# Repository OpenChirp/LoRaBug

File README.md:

# Specs
* TI CC2650 MCU with BLE and 802.15.4 support
* SX1276 LoRa radio
* Provide 500mA 3.3V (3.3-3.4V) from USB.

# Board Details
* Pin mappings are detailed in the spreadsheet found [here](https://docs.google.com/spreadsheets/d/1lk55i37ZrpTx_7zy1oA4uAmHo3XsjOCir2L95xEN9fU/edit?usp=sharing).
* Board physical dimensions and header placement can be found [here](https://docs.google.com/drawings/d/1snO6Dwncqp3OL73APsFgQn0SESudZwlPjw8W5KeOZVo/edit?usp=sharing).
* You can find other information, such as the schematic and board renderings, in the [Info](Info/) directory.

# Firmware Notes
* You can detect the presence of a USB by checking if the FTDI TX and RX
  pins are high. When the FTDI chip is activated, it pulls the TX and RX
  lines high.
  Additionally, this means the CC2650 should use push/pull and no pull-ups 
  when communicating with the FTDI.

# Info
* The power supported by the USB is limited by the 500mA limit of diode D3 and the 600mA limit of the voltage regulator U9.
* When using USB power, the 3.3V rail may swing to 3.4V. This is due to the linear regulator's ground pin voltage being raised by the inline mosfet Q4.
* The SX1276 is said to be only able to support PA_BOOST +20dBm TX when the input voltage is greater than 2.4V. See section 5.4.3 in the [SX1276 datasheet][sx1276_datasheet].

# Low Power Profile
Other than the reverse leakage current, these values are totally unconfirmed. The values are pulled straight from the [datasheet][sx1276_datasheet].

* Reverse leakage from battery through voltage regulation circuitry has shown to draw upwards of **80 nA**. Based on the datasheets, there is a possibility of 0.1 - 0.2uA draw.
* [CC2650][cc2650_overview]
    - Normal operation between 1.8 V and 3.8 V
    - The main MCU crystal is 24 MHz, which is doubled internally. There is also a 32 kHz clock for BLE. See section 6.9 in [overview datasheet][cc2650_brief_datasheet].
    - Active-Mode draws **61 uA/MHz**
    - Active-Mode Sensor Controller draws **8.2 uA/MHz**
    - Standby draws **1 uA** (RTC Running and RAM/CPU Retention)
    - Shutdown draws **100 nA** (Wake Up on External Events)
    - Active-Mode RX draws **5.9 mA**
    - Active-Mode TX at 0 dBm draws **6.1 mA**
    - Active-Mode TX at +5dBm draws **9.1 mA**
    - The sensor controller(when cpu freq. scalled) consumes less power than the [MSP430G2X][msp430_overview], which consumes 220 uA/MHz in active-mode and 0.7 uA in RTC mode.
* [SX1276][sx1276_overview]
    - Up to +17 dBm of RF output power which is maintained from 1.8 V to 3.7 V and +20 dBm from 2.4 V to 3.7 V. See section 5.1 of [datasheet][sx1276_datasheet].
    - We have PA_BOOST connected to the HF (high frequency) side antenna. This means we output 915MHz HF signals through PA_BOOST.
    - LoRa HF RX mode draws **10.3 mA**(125kHz bw) or **12.6 mA**(500kHz bw) with LNABoost off. See sections 2.5.1 and 2.5.5 of [datasheet][sx1276_datasheet].
    - LoRa HF TX mode draws around **90 mA** for +17dBm PA_BOOST and somewhere around **120 mA** for +20dBm PA_BOOST.
    - Sleep mode draws **0.2 uA**
    - Idle mode (RC oscillator enabled) draw **1.5 uA**
    - Standby mode (Crystal oscillator enabled) draw **1.6 mA**

# Changelog
* V3.1
    - Removed inverter and pullup/pulldown resistors from LoRa radio module for power saving
    - Mapped RF_CTRL1 and RF_CTRL2 as complement control pair for RF switches for power saving
    - Resolved SX1276 crystal caps manufacturing issue
* V3
    - Changed IO header to a 20pin 1.27mm for ease of use
    - Access to VCC_NREG, the power feeding the onboard regulator
    - Active low button
    - FTDI TX/RX lines pulled into header
    - Removed onboard I2C resistors
* V2
    - Fixed button NC/NO leads. Pulldown now pulls the signal low as initially designed.
    - Fixed leakage current through the linear regulator
    - Changed FTDI footprint to have longer leads for hand soldering
    - Used a single dual N-channel mosfet chip to control LEDs
    - Changed the fiducial location
    - Changed some components to consolidate count
* V1 - Initial Release

# Contribution Info

## Generating Manufacturer Files
To generate the manufacturer files for APCircuits.com, you need to generate the Gerbers(with outline), Aperture file, and NC Drill file.

To generate the gerbers and aperture files, do the following:
1. Click File -> Fabrication Output -> Gerber Files, when viewing a PCB Layout.
2. Make sure that Top Overlay, Top Paste, Top Solder, Top Layer, Bottom Layer, Bottom Solder, Bottom Overlay(optional), and Mechanical 1 are selected in the Layers tab.
3. Do not have anything selected in the Drill Drawing tab, and make sure that "Embedded aperture (RS274X)" is selected in the Aperture tab.
4. Press Ok.

To generate the NC Drill File, do the following:
1. Click File -> Fabrication Output -> NC Drill Files, when viewing a PCB Layout.
2. Just click Ok to the default settings.

To generate the pick and place coordinates file:
1. Click File -> Assembly Outputs -> Generate pick and place files
2. Ensure only the Text and Imperial options are checked and click Ok

The previous operations place all the output files in the "Project Output for LoRaBugBoard" directory.
You now just need to combine the following list of file into a zip archive. Make sure to copy in the
README.txt from previous archives.

Archive File List:

* PCBFireflyCaseV3.apr
* PCBFireflyCaseV3.DRR
* PCBFireflyCaseV3.GBL
* PCBFireflyCaseV3.GBO
* PCBFireflyCaseV3.GBS
* PCBFireflyCaseV3.GM1
* PCBFireflyCaseV3.GTL
* PCBFireflyCaseV3.GTO
* PCBFireflyCaseV3.GTP
* PCBFireflyCaseV3.GTS
* PCBFireflyCaseV3-RoundHoles.TXT
* PCBFireflyCaseV3-SlotHoles.TXT
* Pick Place for PCBFireflyCaseV3.txt
* README.txt

## Testing the Hardware
* ***Test FTDI, System UART, Bootloader Backdoor Trigger, and Onboard Voltage Regulator***
  Ensure that the bootloader backdoor is configured to use the button. Ensure R20 is low enough to not trigger the bootloader after reset.
  I previously had an issue where the pulldow(at the time) wasn't strong enough. Next, ensure you can actually enter the bootloader during reset.
  To aid in this, I created a script called [trigger_bootloader.sh](Info/trigger_bootloader.sh) in the Info directory that sends the initialization
  bytes to serial repeatedly. If you cat the serial device at the same time, you should see the bootloader respond.
  Maybe do a `stty -F /dev/ttyUSB0 115200 && cat /dev/ttyUSB0 | hd`. Checkout the [CC2650 Bootloader Spec][cc2650_bootloader_spec].
* ***Test LEDs***
* ***Test Pins in GPIO Hedaer***
* ***Test Debugging CC2650 Over Cortex Debug Header***
* ***Test SX1276 Front End***

# Antennas

| Description | Part Name   | Manufacturer | Connector |
| ------------| ----------- | ------------ | --------- |
| Standard yellow 915MHz LoRa 5.591" 1.2dBi | [NT-916-CW-HWR-SMA](http://www.linxtechnologies.com/resources/data-guides/ant-916-cw-hwr.pdf) | Linx Technologies | SMA-Male |
| ~~4.256" 900MHz 3.0dBi~~ | ~~[APAMS-118](http://abracon.com/external-antenna/APAMS-118.pdf)~~ | ~~Abracon LLC~~ | ~~SMA-Male~~ |

# Accessories

The board was designed to accept an **RFI shield** over the LoRa radio components.
You can solder on a static can or use the two part removable can.
* Static can [BMI-S-103](http://www.digikey.com/products/en?keywords=BMI-S-103). The preferred low-profile can is the BMI-S-111 by Laird.
* Removable two part: The frame is [BMI-S-203-F](http://www.digikey.com/products/en?keywords=BMI-S-203-F) and the cover is [BMI-S-203-C](http://www.digikey.com/products/en?keywords=BMI-S-203-C).
* You can use a 10pin 1.27mm female-to-female IDC cable to connect the CC2650 Launchpad debugger.
  One such cable is the [Harwin M50 Female-to-Female](https://www.digikey.com/product-detail/en/harwin-inc/M50-9100542/952-2568-ND/4953091) cable.
* The SensorBug board uses a Tag-Connect TC2030 pin interface to pass JTAG through to the LoRaBug.
  You can use the [TC2030-CTX](http://www.tag-connect.com/TC2030-CTX) cable to connect the
  CC2650 Launchpad debugger.

The I/O header is a standard 1.27mm 2x10 pin header.
You can use the [Harwin M50-3121045](http://www.digikey.com/products/en?keywords=M50-3121045) to interface with it.

[cc2650_overview]: http://www.ti.com/product/CC2650
[cc2650_brief_datasheet]: http://www.ti.com/lit/ds/symlink/cc2650.pdf
[sx1276_overview]: http://www.semtech.com/wireless-rf/rf-transceivers/sx1276/
[sx1276_datasheet]: http://www.semtech.com/images/datasheet/sx1276_77_78_79.pdf
[msp430_overview]: http://www.ti.com/lsds/ti/microcontrollers_16-bit_32-bit/msp/ultra-low_power/msp430g2x_i2x/overview.page
[cc2650_bootloader_spec]: http://www.ti.com/lit/an/swra466a/swra466a.pdf

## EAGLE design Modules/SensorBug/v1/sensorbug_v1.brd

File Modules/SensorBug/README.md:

# SensorBug

An environmental sensor board with a Grid-EYE IR sensor array

## Sensors

1. Panasonic Grid-EYE AMG8833
2. Passive Infrared (Motion) Sensor - Panasonic EKMB1201112
3. Ambient Light Sensor - Panasonic PNJ4K01F
4. Accelerometer/Absolute Orientation Sensor - Bosch BMX160
5. Environmental Sensor - Bosch BME680
6. MEMS Microphone - Knowles SPU0410LR5H

## Other components
* Macronix MX25R8035FZUIL0 SPI 8Mb NOR Flash chip
* Domain 1 Regulator - [LP5951MF-1.8](http://www.ti.com/lit/ds/symlink/lp5951.pdf)
* Domain 2 P-Channel Mosfet - [DMP3010LK3](https://www.diodes.com/assets/Datasheets/DMP3010LK3.pdf)

# Header Pins Usage

| Near Power Pads             | Near MCU        |
| --------------------------- | --------------- |
| 3V3                         | GND             |
| 3V3                         | GND             |
| -                           | -               |
| -                           | -               |
| -                           | I2C SDA         |
| Pwr Domain1 EN (Flash nCS)  | I2C SCL         |
| Light Analog                | Flash MOSI      |
| Mic Analog                  | Flash CLK       |
| BMX INT 1                   | Flash MISO      |
| PIR Digital                 | Pwr Domain2 nEN |

# Power Domains

## Alway On
* PIR                           - 1uA
* Accelerometer (BMX160)        - 5uA in suspend
* Environmental Sensor (BME680) - 0.15uA in suspend

## Domain 1
Domain 1 is controlled by a 1.8V linear regulator. The Domain 1 enable signal toggles the regulator's active high enable pin.

* Ambient Light Sensor
* Microphone

## Domain 2
Domain 2 is controlled by a p-channel mosfet, thus the enable signal is active low.

* GridEye
* SPI Flash

# Protocols

| Sensor       | Protocol    |
| ------------ |------------ |
| Flash        | SPI         |
| BMX160       | I2C, INT    |
| BME680       | I2C         |
| Light        | Analog      |
| Mic          | Analog      |
| PIR          | Digital     |
| GridEye      | I2C         |

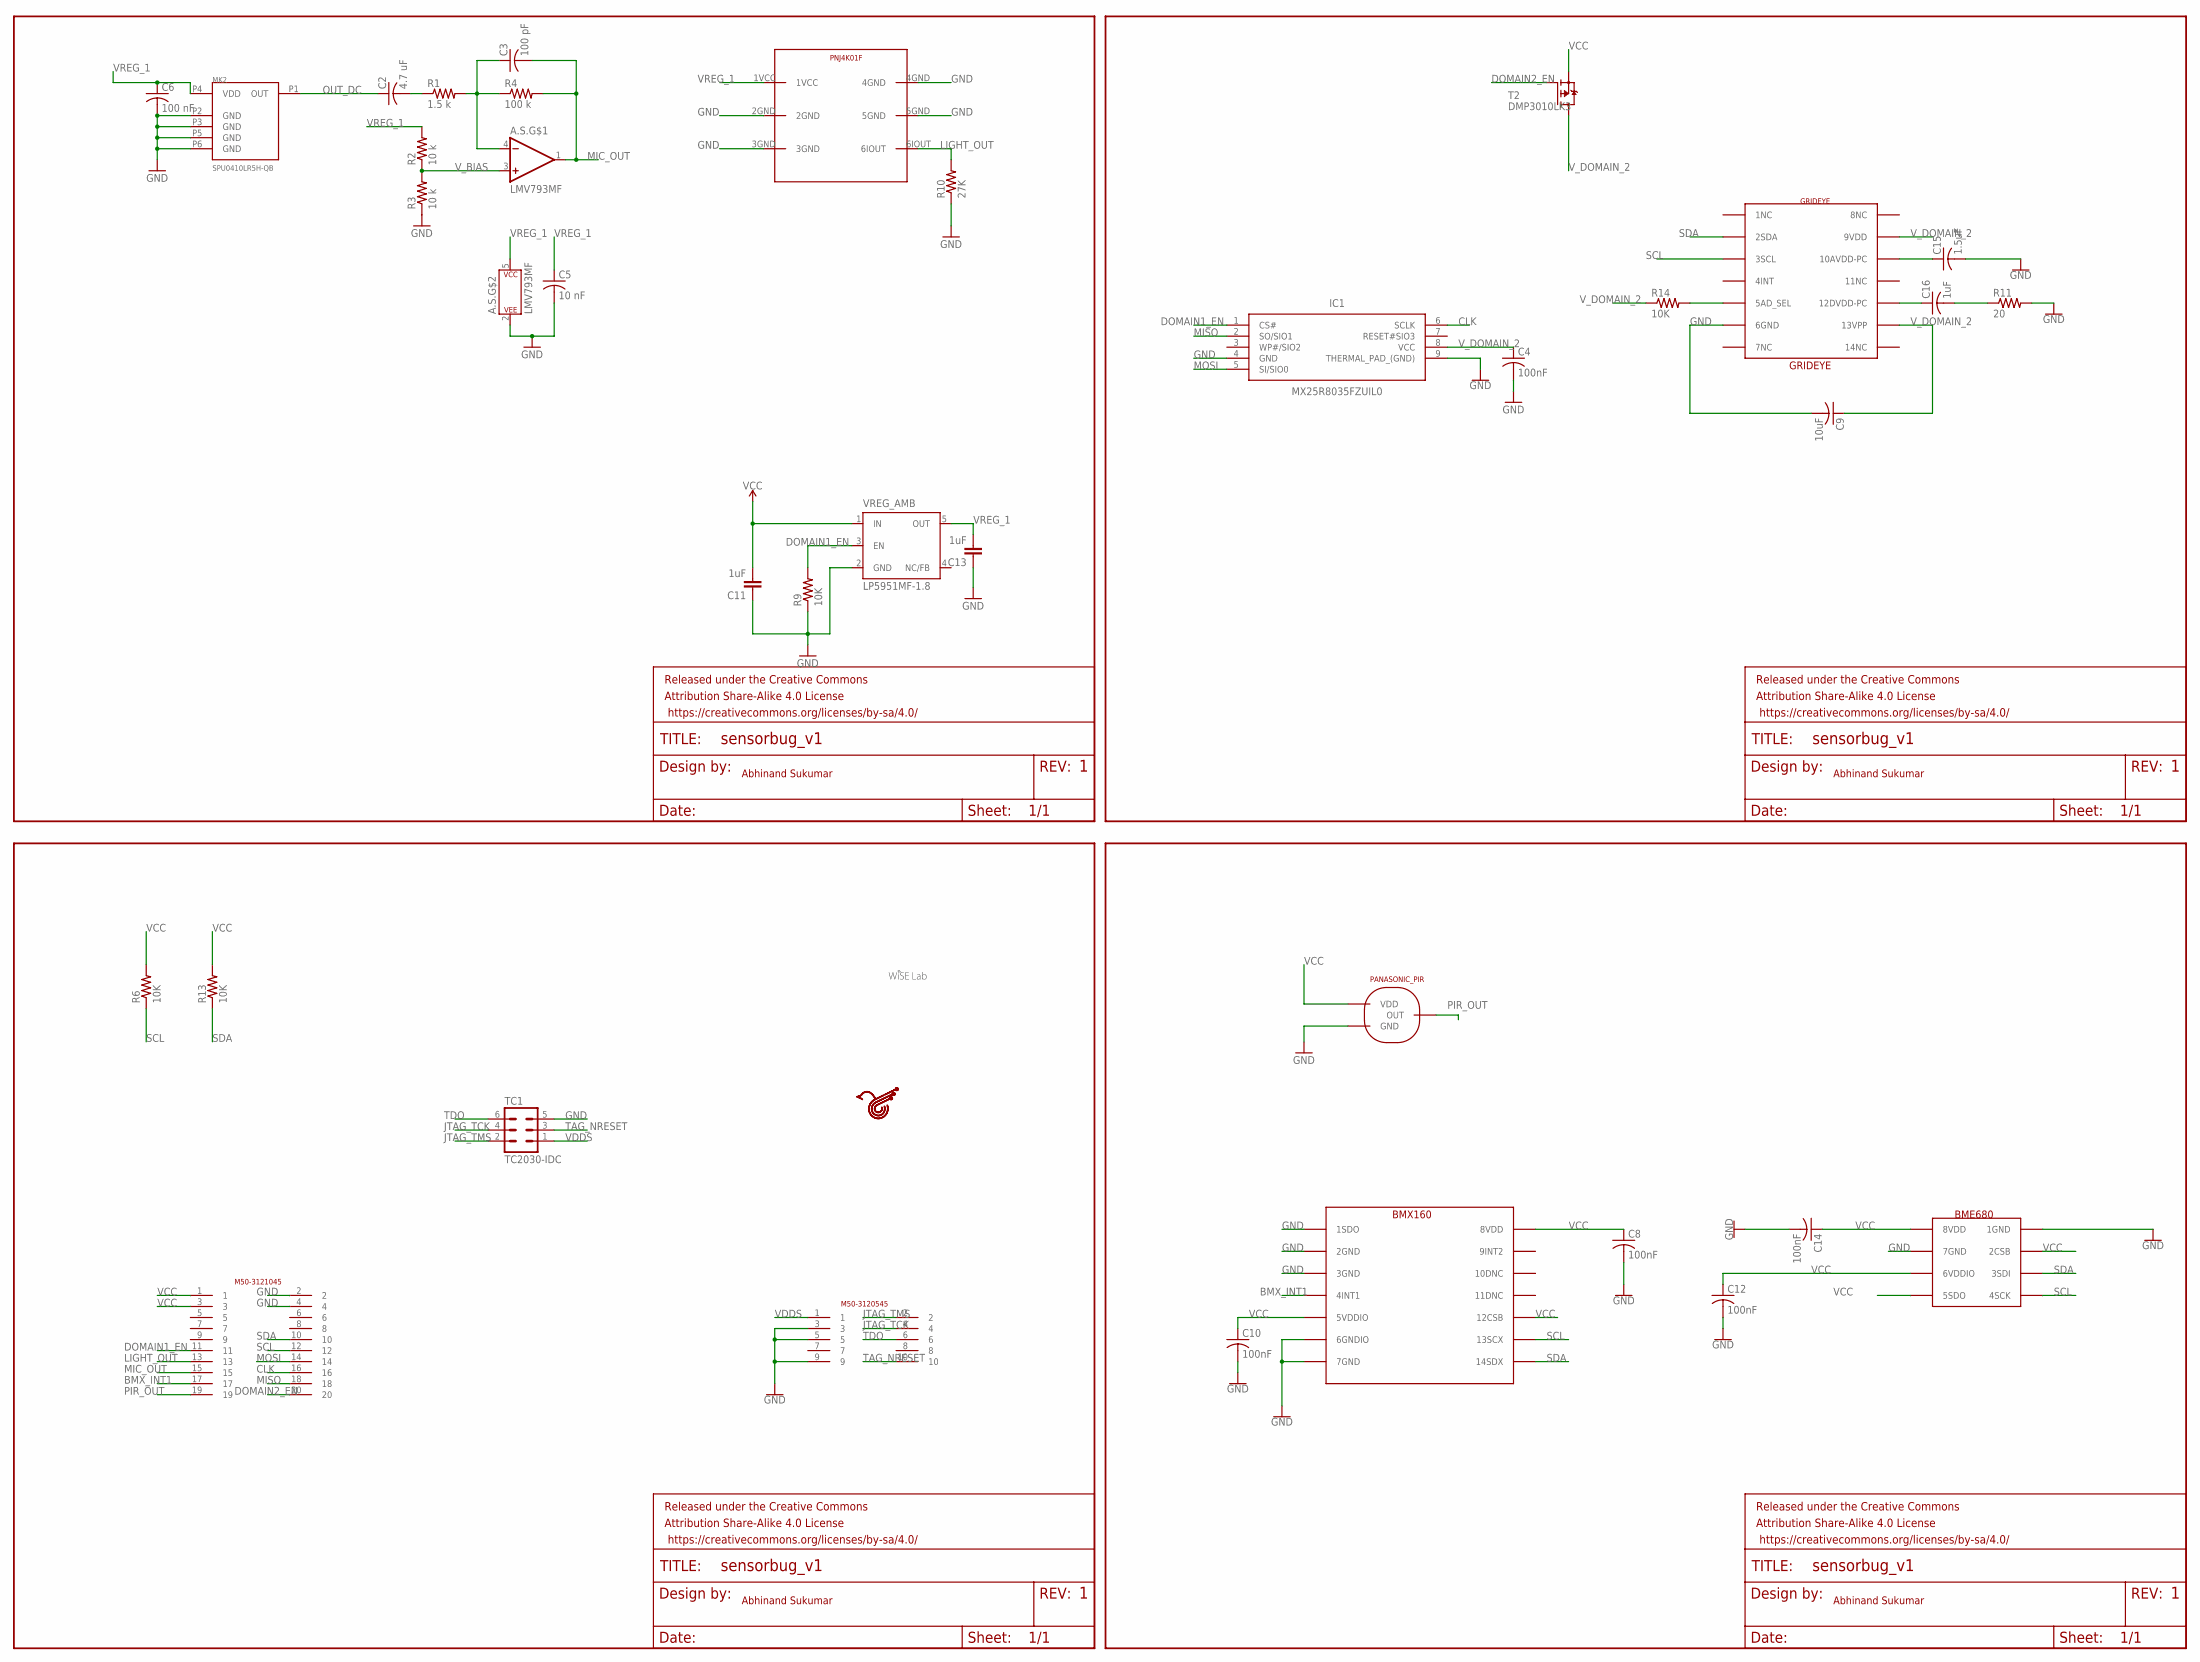
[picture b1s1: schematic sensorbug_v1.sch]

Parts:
A.S.: LMV793MF; SOT23-5
BME: BME680; BME680_LGA
BMX: BMX160; LGA
C2: 4.7 uF; C0603
C3: 100 pF; C0603
C4, C8, C10, C12, C14: 100nF; C0603
C5: 10 nF; C0603
C6: 100 nF; C0603
C9: 10uF; C0603
C11, C13, C16: 1uF; C0603
C15: 1.5uF; C0603
FRAME1, FRAME2, FRAME3, FRAME4: FRAME-LETTER; CREATIVE_COMMONS
GRIDEYE: GRIDEYE
IC1: MX25R8035FZUIL0; USON-8L
LIGHT: PNJ4K01F
MK2: SPU0410LR5H-QB
R1: 1.5 k; R0603
R2, R3: 10 k; R0603
R4: 100 k; R0603
R6, R9, R13, R14: 10K; R0603
R10: 27K; R0603
R11: 20; R0603
T2: DMP3010LK3; TO252
TC1: TC2030-IDC
U$2: WISELAB_LOGO-M; WISELAB_LOGO_M
U$3: EKMB1201112
U$4: M50-3121045
U$5: M50-3120545; M50-3100545
U$6: OPENCHIR_LOGO_PCB-M; OPENCHIRP_LOGO_M
VREG_AMB: LP5951MF-1.8; SOT23-DBV

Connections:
BMX_INT1: BMX.4INT1, U$4.17
CLK: IC1.6 (SCLK), U$4.16
DOMAIN1_EN: IC1.1 (CS#), R9.2, U$4.11, VREG_AMB.3 (EN)
DOMAIN2_EN: T2.1 (G), U$4.20
GND: A.S..2 (P$V-), BME.1GND, BME.7GND, BMX.1SDO, BMX.2GND, BMX.3GND, BMX.6GNDIO, BMX.7GND, C4.2, C5.2, C6.2, C8.2, C9.2, C10.2, C11.1, C12.2, C13.1, C14.2, C15.2, GRIDEYE.6 (6GND), IC1.4 (GND), IC1.9 (THERMAL_PAD_(GND)), LIGHT.2GND, LIGHT.3GND, LIGHT.4GND, LIGHT.5GND, MK2.P2 (GND), MK2.P3 (GND), MK2.P5 (GND), MK2.P6 (GND), R3.1, R9.1, R10.1, R11.2, TC1.5, U$3.GND, U$4.2, U$4.4, U$5.3, U$5.5, U$5.9, VREG_AMB.2 (GND)
JTAG_TCK: TC1.4, U$5.4
JTAG_TMS: TC1.2, U$5.2
LIGHT_OUT: LIGHT.6IOUT, R10.2, U$4.13
MIC_OUT: A.S..1 (OUT), C3.2, R4.2, U$4.15
MISO: IC1.2 (SO/SIO1), U$4.18
MOSI: IC1.5 (SI/SIO0), U$4.14
unnamed: C15.1, GRIDEYE.10 (10AVDD-PC)
unnamed: A.S..4 (-IN), C3.1, R1.2, R4.1
unnamed: C16.1, GRIDEYE.12 (12DVDD-PC)
unnamed: GRIDEYE.5 (5AD_SEL), R14.2
unnamed: C16.2, R11.1
OUT_AC: C2.2, R1.1
OUT_DC: C2.1, MK2.P1 (OUT)
PIR_OUT: U$3.OUT, U$4.19
SCL: BME.4SCK, BMX.13SCX, GRIDEYE.3 (3SCL), R6.1, U$4.12
SDA: BME.3SDI, BMX.14SDX, GRIDEYE.2 (2SDA), R13.1, U$4.10
TAG_NRESET: TC1.3, U$5.10
TDO: TC1.6, U$5.6
VCC: BME.2CSB, BME.5SDO, BME.6VDDIO, BME.8VDD, BMX.5VDDIO, BMX.8VDD, BMX.12CSB, C8.1, C10.1, C11.2, C12.1, C14.1, R6.2, R13.2, T2.2 (S), U$3.VDD, U$4.1, U$4.3, VREG_AMB.1 (IN)
VDDS: TC1.1, U$5.1
VREG_1: A.S..5 (P$V+), C5.1, C6.1, C13.2, LIGHT.1VCC, MK2.P4 (VDD), R2.2, VREG_AMB.5 (OUT)
V_BIAS: A.S..3 (+IN), R2.1, R3.2
V_DOMAIN_2: C4.1, C9.1, GRIDEYE.9 (9VDD), GRIDEYE.13 (13VPP), IC1.8 (VCC), R14.1, T2.3 (D)

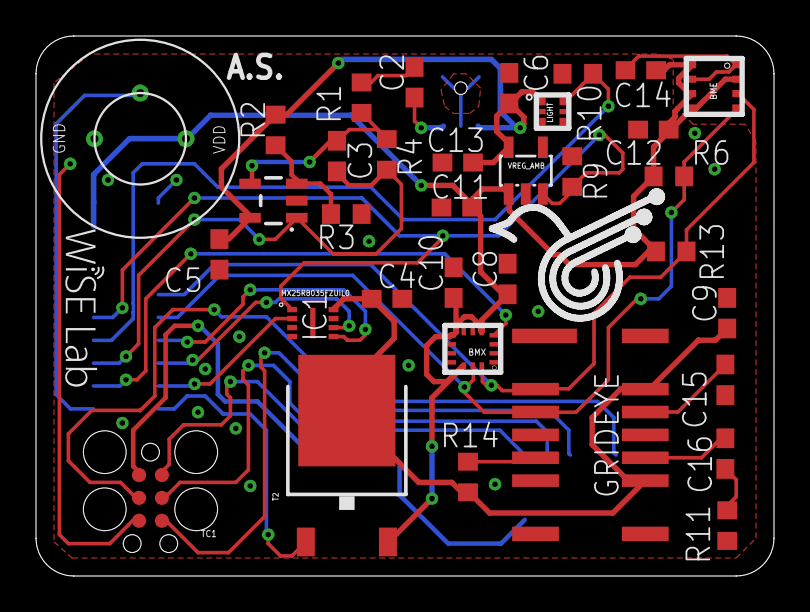
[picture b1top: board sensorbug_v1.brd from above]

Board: 2 copper layers, 41.0 x 30.0 mm, 43 parts (1 on the bottom side), 28 nets.

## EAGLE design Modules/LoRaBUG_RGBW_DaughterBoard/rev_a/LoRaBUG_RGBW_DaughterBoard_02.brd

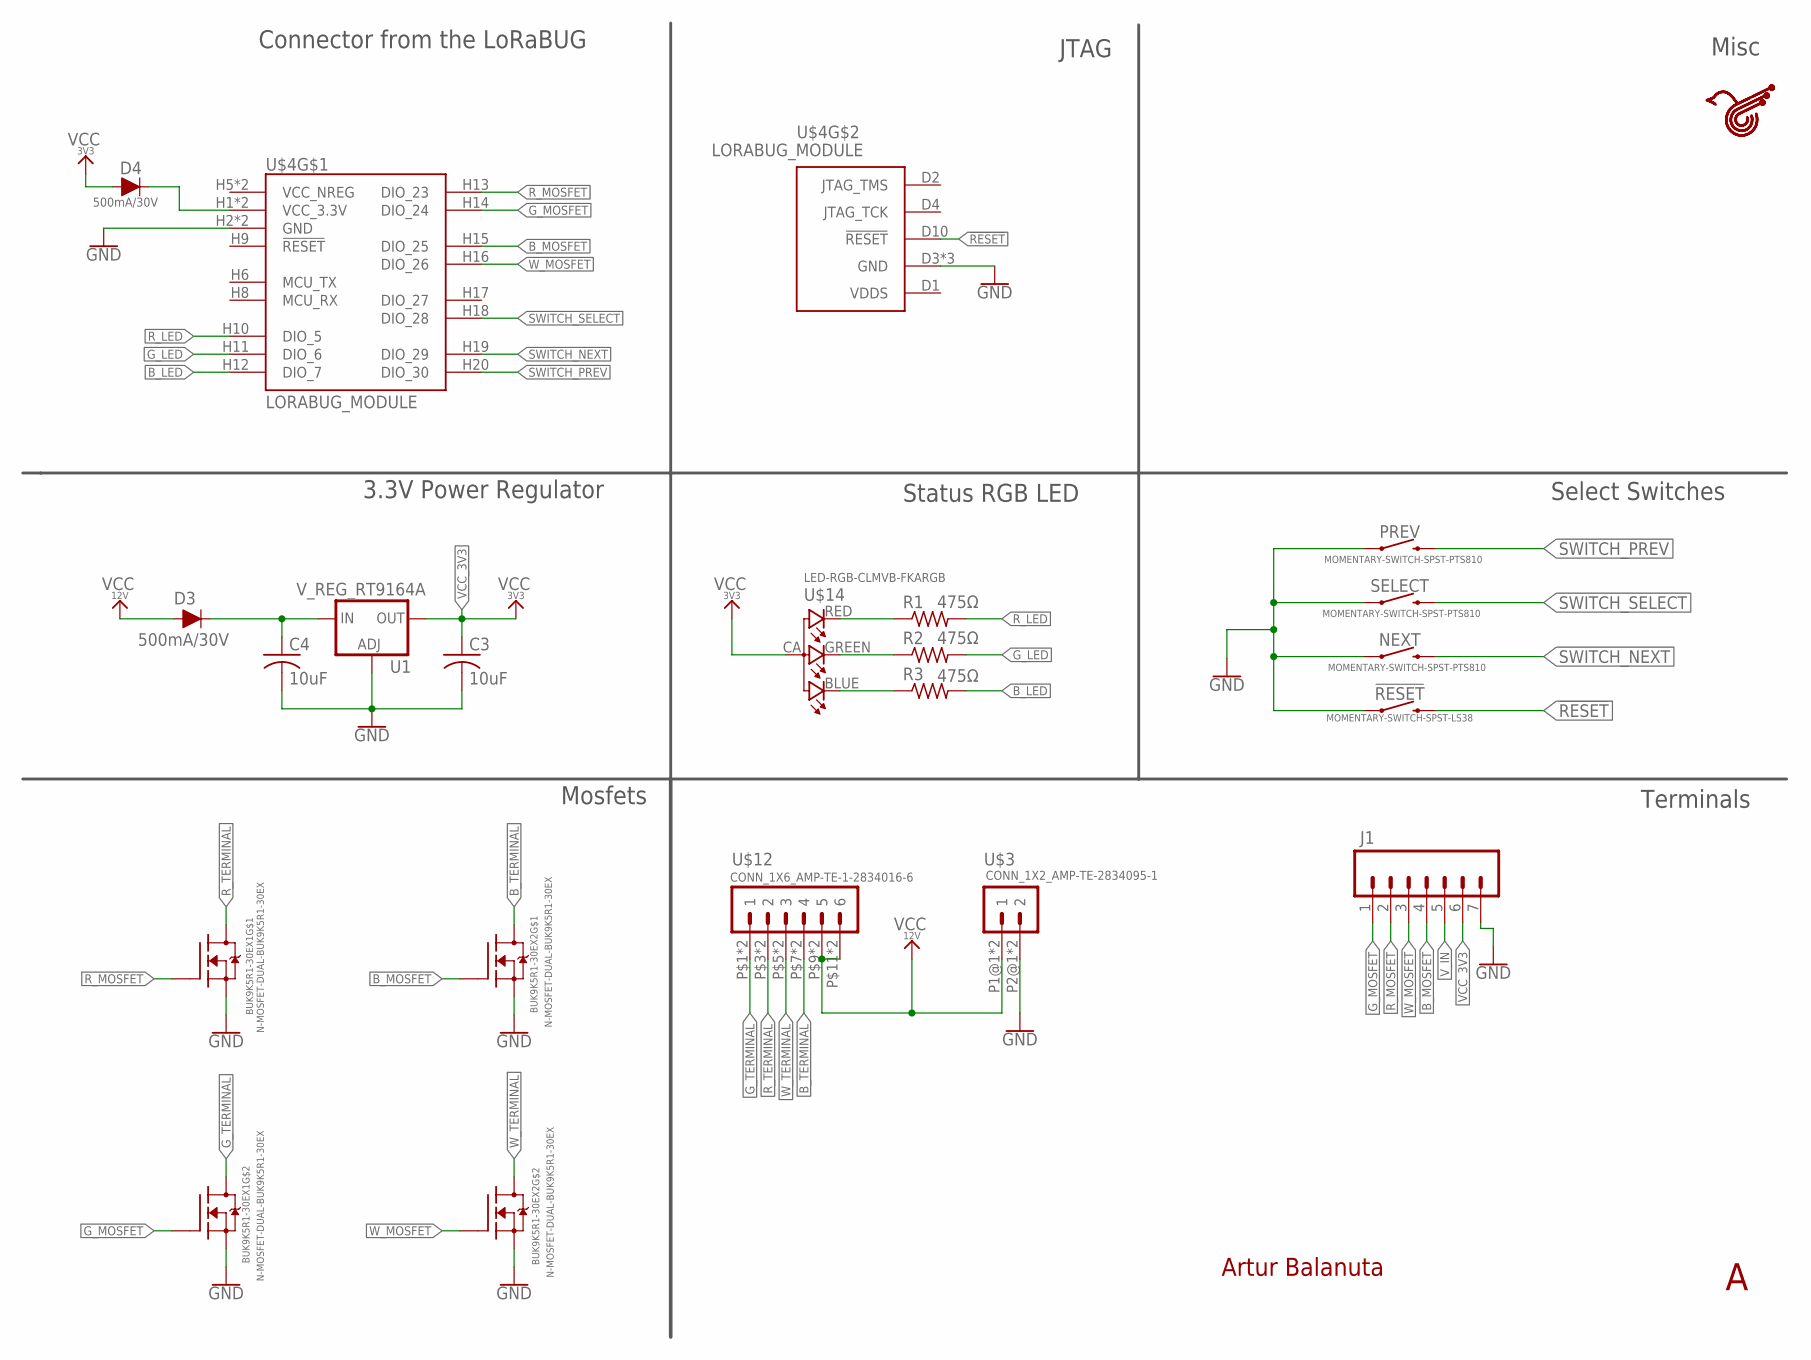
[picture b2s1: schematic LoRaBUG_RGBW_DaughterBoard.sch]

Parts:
!RESET: MOMENTARY-SWITCH-SPST-LS38; TACTILE_SWITCH_SMD_3.3X3.1MM_LS38
BUK9K5R1-30EX1, BUK9K5R1-30EX2: N-MOSFET-DUAL-BUK9K5R1-30EX; LFPAK56D
C3, C4: 10uF; C0603K
D3, D4: 500mA/30V; SOD-323
J1: CONN_07NO_SILK; 1X07_NO_SILK
NEXT: MOMENTARY-SWITCH-SPST-PTS810; TACTILE_SWITCH_SMD_4.2X3.2MM
PREV: MOMENTARY-SWITCH-SPST-PTS810; TACTILE_SWITCH_SMD_4.2X3.2MM
R1, R2, R3: 475Ω; R0603
SELECT: MOMENTARY-SWITCH-SPST-PTS810; TACTILE_SWITCH_SMD_4.2X3.2MM
U1: V_REG_RT9164A; SOT223
U$3: CONN_1X2_AMP-TE-2834095-1
U$4: LORABUG_MODULE
U$5: OPENCHIR_LOGO_PCB; OPENCHIRP_LOGO_S
U$12: CONN_1X6_AMP-TE-1-2834016-6
U$14: LED-RGB-CLMVB-FKARGB; PLCC4-2MM-RGB

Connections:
!RESET: !RESET.P$3 (2), !RESET.P$4 (2), U$4.D10 (!RESET)
B_LED: R3.2, U$4.H12 (DIO_7)
B_MOSFET: BUK9K5R1-30EX2.P$2 (G), J1.4, U$4.H15 (DIO_25)
B_TERMINAL: BUK9K5R1-30EX2.P$7 (D), BUK9K5R1-30EX2.P$8 (D), U$12.P$7 (4), U$12.P$8 (4)
GND: !RESET.P$1 (1), !RESET.P$2 (1), BUK9K5R1-30EX1.P$1 (S), BUK9K5R1-30EX1.P$3 (S), BUK9K5R1-30EX2.P$1 (S), BUK9K5R1-30EX2.P$3 (S), C3.2, C4.2, J1.7, NEXT.P$1 (1), NEXT.P$2 (1), PREV.P$1 (1), PREV.P$2 (1), SELECT.P$1 (1), SELECT.P$2 (1), U1.1 (ADJ), U$3.P2@1 (2), U$3.P2@2 (2), U$4.D3 (GND), U$4.D5 (GND), U$4.D9 (GND), U$4.H2 (GND), U$4.H4 (GND)
G_LED: R2.2, U$4.H11 (DIO_6)
G_MOSFET: BUK9K5R1-30EX1.P$4 (G), J1.1, U$4.H14 (DIO_24)
G_TERMINAL: BUK9K5R1-30EX1.P$5 (D), BUK9K5R1-30EX1.P$6 (D), U$12.P$1 (1), U$12.P$2 (1)
unnamed: R1.1, U$14.RED (4)
unnamed: R2.1, U$14.GREEN (3)
unnamed: R3.1, U$14.BLUE (2)
N_VIN: C4.1, D3.C, U1.3 (IN)
R_LED: R1.2, U$4.H10 (DIO_5)
R_MOSFET: BUK9K5R1-30EX1.P$2 (G), J1.2, U$4.H13 (DIO_23)
R_TERMINAL: BUK9K5R1-30EX1.P$7 (D), BUK9K5R1-30EX1.P$8 (D), U$12.P$3 (2), U$12.P$4 (2)
SWITCH_NEXT: NEXT.P$3 (2), NEXT.P$4 (2), U$4.H19 (DIO_29)
SWITCH_PREV: PREV.P$3 (2), PREV.P$4 (2), U$4.H20 (DIO_30)
SWITCH_SELECT: SELECT.P$3 (2), SELECT.P$4 (2), U$4.H18 (DIO_28)
VCC_3V3: C3.1, D4.A, J1.6, U1.2 (OUT), U1.4 (OUT), U$14.CA (1)
VCC_12V: D3.A, U$3.P1@1 (1), U$3.P1@2 (1), U$12.P$9 (5), U$12.P$10 (5), U$12.P$11 (6), U$12.P$12 (6)
VCC_NREG: U$4.H5 (VCC_NREG), U$4.H7 (VCC_NREG)
VDDS: U$4.D1 (VDDS)
V_IN: D4.C, J1.5, U$4.H1 (VCC_3.3V), U$4.H3 (VCC_3.3V)
W_MOSFET: BUK9K5R1-30EX2.P$4 (G), J1.3, U$4.H16 (DIO_26)
W_TERMINAL: BUK9K5R1-30EX2.P$5 (D), BUK9K5R1-30EX2.P$6 (D), U$12.P$5 (3), U$12.P$6 (3)

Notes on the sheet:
Connector from the LoRaBUG
Artur Balanuta
3.3V Power Regulator
Status RGB LED
Select Switches
Terminals
Mosfets
JTAG
Misc

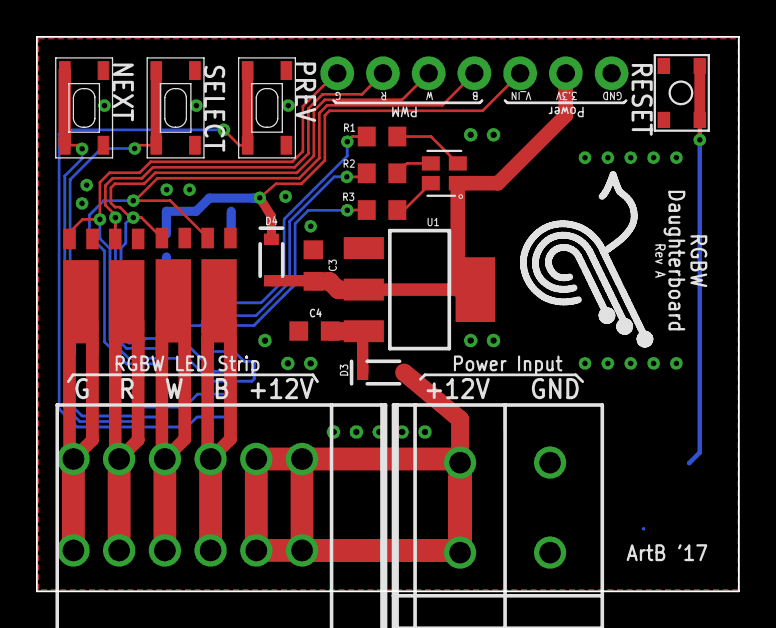
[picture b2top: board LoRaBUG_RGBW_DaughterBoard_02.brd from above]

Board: 2 copper layers, 39.0 x 30.8 mm, 20 parts (0 on the bottom side), 24 nets.

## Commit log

2016-06-03 Semtech SX1276 schematic and initial work on the TI CC2650 schematic.
2016-06-03 Fixed missing Semtech and TI libraries
2016-06-03 Fixed TI chip - changed from CC13xx to CC26xx. Completed RF side of CC2650 schematic.
2016-06-10 First version
2016-06-10 Adding first version PDF of schematic
2016-06-14 Recovered and updated SX1276Radio schematic
2016-06-14 Modified Adwait's board lib to not include antenna and outline
2016-06-14 Removed miscellaneous component_1 from TI library
2016-06-14 Updates to schematics and project
2016-06-14 Base PCB board design. No elements placed.
2016-06-14 Added gitignore
2016-06-14 Progress laying out PCB
2016-06-17 More routing and general progress
2016-06-21 Work in progress. * Fixed missing VCC_ANA * Added some 3D models * Changed/deleted buttons * Simplified power * Removed small header * Shrunk FTDI decoup caps * Routed more * More that I can't recall
2016-06-21 Updated schematic/pcb pdf
2016-06-22 Unified Connectors Library and added 3D models
2016-06-22 Cleanup and update
2016-06-22 Big changes and corrections
2016-06-22 Updated schematic PDF with routing progress
2016-06-23 Corrected errors in schematic and routing progress. Nearly finished routing.
2016-06-24 Second time redoing the new RFI Shield 26.21x26.21mm
2016-06-24 Repositioned the RFI Shield origin
2016-06-25 Added in new RFI shield that I do not currently use anymore.
2016-06-25 Modified schematic to fit PCB a bit and progress routing
2016-06-25 Updated schematic/pcb layout PDF
2016-06-27 Changed RFI shield to use pads instead of polygon fills. This allows the ground plane fill to attach itself to the contacts.
2016-06-27 Bug fixes in schematic. One big one is VDD* vs VSS* labeling conflict with SX schematic
2016-06-27 Disconnect SPI from header
2016-06-27 Partial surgery underway. One bottom of CC2650 must be routed.
2016-06-27 Updated schematic PDF and PCB layout
2016-06-28 Before major surgery on the PCB
2016-06-28 Changes to schematic
2016-06-28 Routing complete with some GND vias
2016-06-28 Routing complete. Needs ground planes.
2016-06-29 Before pouring the ground plane
2016-06-29 Added surface mount SMA connector back into the CC2650 schematic
2016-06-29 Added in the surface mount SMA connector
2016-06-29 Added in an inverted F antenna to ExtraComponents with no solder mask or paste.
2016-06-29 Removed voltage non-regulated from battery supply 3.3v
2016-06-29 Updated CC2650 to use new inverted F antenna
2016-06-29 Fixed voltage unregulated disconnect in PCB. Before reshaping board to include triangle corners
2016-06-29 Resized board to include inside triangle corners
2016-06-30 Complete v1
2016-06-30 Update schematic and PCB layout PDF.
2016-06-30 Added via stitching
2016-07-01 Switched LED control lines. No copper constraint violations.
2016-07-01 Completley routed v1
2016-07-02 LoRaBug Version 1
2016-07-05 Regenerated Gerber files with new mechanical layer 1
2016-07-05 Added in Top Paste layer
2016-07-05 Regenerated gerbers again. Now with Top Paste
2016-07-05 Added in BOM xls
2016-07-05 Slight improvement of schematic/pcb
2016-07-15 Included BOM
2016-07-15 New PDF in info directory
2016-07-15 Updated schematics and PCB silkscreen positions
2016-07-15 Added in notes
2016-07-15 Changed mosfets to PERIPH category
2016-08-03 Fixed button NC/NO pin error. Added proper fiducials to schematic.
2016-08-03 Updated silk screen, initials, and fiducials
2016-08-03 Updated BOM
2016-09-16 Added new Dual Mosfet, VREG, and Diodes to ExtraComponents
2016-09-16 Simplified mosfets for LED to single dual mosfet chip
2016-09-16 Fixed reverse power leakage in VREG design and increased power output of VREG
2016-09-16 Created new board layout for final version 2 design
2016-09-16 Updated project
2016-09-20 Remove .OutJob file from project
2016-09-20 Changed VREG mosfet switch to the dual mosfet due to size constraints
2016-09-20 Components placed, routing almost complete
2016-09-21 Swapped LED connections on dual mosfet for better PCB layout Cleaned up schematics
2016-09-21 Finished vreg power leakage fix
2016-09-21 Created a README.md with some specs, info, and changelog
2016-09-21 Typo fix in README.md
2016-09-21 Added a few more specs to README
2016-09-21 Removed FTDI lib from libraries, since FTDI chip is in ExtraComponents lib
2016-09-21 Updated version to v2 on PCB
2016-09-21 Added new footprint for FTDI with long leads. Changed FTDI module schematic to use new footprint
2016-09-21 Created new PCB layout with the new long-lead FTDI footprint
2016-09-21 Merged FTDI Fixed PCB layout into the PCBFireflyCaseV2
2016-09-21 Changed R20 from 0402 to 0603 to consolidate components
2016-09-21 Updated diode description and deleted TODO
2016-09-21 Updated BOM for with V2 components
2016-09-21 Updated README to reflect FTDI lead extension
2016-09-21 Updated version/revision to 2
2016-09-21 Generated new version 2 PDf with schematics and pcb layout
2016-09-21 Wrote instructions in README.md for generateing manufacturer files
2016-09-21 Generated new manufacturer files for V2
2016-09-21 Added 3D image of V2 board
2016-09-22 Added screenshots of online ordering through APCircuits
2016-10-05 Changed LoRaBugBoardV2.pdf to include the PCB without the GND fill planes.
2016-10-14 Changed R17 and R18 to be specific for LEDs D1 and D2
2016-10-14 Change TICC2650 to the cheaper higher quantity MCU package, the CC2650F128RGZR instead of CC2650F128RGZT.
2016-10-14 Changed crystal cap to 10pF. Changed sorted LoRa module sheet to take precedence.
2016-10-14 Added FTDI parts list Reorganized all columns
2016-10-14 Added some antennas to BOM
2016-10-16 Added some antenna info to the README.md
2016-10-17 Fixed formatting in file list of README.md
2016-10-17 Added pin mappings spreadsheet link to README.md and pointed to the Info directory
2016-10-26 Added some power details about the components on the board
2016-10-26 Fixed some cc2650 details
2016-10-28 Changed note about reverse leakage current
2016-10-28 EE typo
2016-10-29 Switched diode to new 0 leakage version and organized a bit
2016-10-29 Added more pictures of LoRaBugBoard with the enclosure
2016-10-31 Added mention of RFI cans in README.md
2016-10-31 Added RFI can options to Hardware sheet in BOM
2016-11-09 Reflected 80nA draw from FTDI+VREG in README.md
2016-11-11 Posted notice of V3 coming soon
2016-11-16 Updated V3 board changelog
2016-11-16 Added new 2x10 1.27mm SMD header to Connectors library
2016-11-16 Added notes and renamed nets in CC1650 module
2016-11-16 Rewired a few nets in SX1276 module in an attempt to fix Altium's net coloring glitch
2016-11-16 Adjusted for peripherals module for new 1.27mm 2x10 header * Changed button to active low * Removed I2C pullups * Added system uart tx/rx to header * Added voltage non-regulated to header
2016-11-16 Pulled power subsystem components out of Main schematic and placed them in new Power schematic * We now explicitly deal with VCC_NREG for non-regulated power
2016-11-16 V3 initial routing
2016-11-16 Saving new Altium project
2016-11-16 Updated Revision count Document Parameter to 3 for all schematics
2016-11-17 Changed footprints and final V3 PCB layout
2016-11-17 Save Altium project
2016-11-17 Adding in LoRaBugBoard V3 PDF of schematics and PCB layout
2016-11-17 Corrected README.md contribution section
2016-11-17 Archived V2 fabrication files
2016-11-17 Updated BOM with new header and Power naming scheme
2016-11-17 Rename sheet in BOM
2016-11-17 Added 3D view of V3 board
2016-11-17 Added 2x5 1.27mm header to Connectors library with low-profile header 3D model
2016-11-17 Final edits to schematic and PCB layout for V3
2016-11-18 Generated fabrication output for V3
2016-11-18 Added link to board dimensions diagram
2016-11-18 Updated Altium project
2016-11-18 Housekeeping in Main.SchDoc
2016-11-18 Minor corrections and improved readability of BOM.xls
2016-11-18 Added script to trigger bootloader on device reset
2016-11-18 Added testing section to README and updated file generation instructions
2016-11-18 Added pick and place file for v3
2016-11-21 Fixed R19 incorrect Part Number and moved D3 up sheet
2016-12-05 Adding in LICENSE
2016-12-08 Made changes for v3.1 in SX1276 radio and PCB
2016-12-08 Updated documentation and schematic documentaion with V3.1 changes
2016-12-08 Generated all fabrication and PDF files for V3.1 Archived V3.0
2016-12-08 Added zip archive of V3.1 fabrication files
2016-12-08 Added new 3D image of V3.1 board
2016-12-09 Updated BOM.xls for V3.1
2017-01-06 Critical Change. Changed LoRa modem crystal caps to 15pF
2017-01-08 Added note about detecting USB from firmware
2017-01-08 Added new low-profile RFI shied to BOM.xls
2017-01-08 Font change in README.md
2017-01-08 Fixed RFI shield links
2017-01-08 Add crystal caps fix to changelog
2017-03-22 Added note about which I/O header to use
2017-03-22 Striked the Abracon antenna out, since it doesn't work well
2017-05-25 Added the revA of the RGBW Module
2017-05-30 Added README.md for introducing Modules
2017-05-30 adds Picture for the RGBW Controller Module
2017-07-11 Added starter directory for SensorBug module
2017-07-12 Added Info and V1 Directories
    Info has a pdf with schematic and board layout. V1 has the schematic,
    board, and gerber files.
2017-07-26 Fixed Light Sensor Output
    Previous light sensor output pin did not have ADC capabilities.
    Interchanged DOMAIN1_EN and LIGHT_OUT.
2018-08-23 Improved the README documentaion for The SensorBug
2018-09-04 The most revolutionary commit in the history of GitHub
2018-09-04 More updates to README.md of SensorBug
2019-01-16 Added notes about debug cable to README.md
2019-02-25 Changed FTDI schematic 3V3 output to a Power pin
2019-02-25 Imported FTDI changes to 3V3 Power pin
2019-02-25 Connected FTDI 3V3 Out to VIO In
2019-02-27 Connected FTDI CBUS4 to MCU DIO1
2019-02-27 Added PCB V4 with changes to FTDI and smaller vias.
2019-02-27 All vias tented now
2019-02-27 Beautification and maximizing GND pours
2019-02-28 Added CC2652R to lib
2019-02-28 Added 48MHz Crystal to lib
2019-02-28 Removed two random wires on the corners of the CC2650 schematic
2019-02-28 Simply replaced cc2650 schematic with duplicate cc2652r schematic
2019-02-28 Integrated new 48MHz crystal and cc2652r
2019-02-28 New via stitiching
2019-02-28 Added 3D preview of LoRaBug V4
2019-02-28 DRC Completion
2019-02-28 Updated BOM with new crystal and cc2652r.
    The crystal can be tweaked to another cx2016db.

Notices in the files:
parts and their libraries:
SparkFun-PowerSymbols: Licensing: Creative Commons ShareAlike 4.0 International - https://creativecommons.org/licenses/by-sa/4.0
SparkFun-Aesthetics: Released under the Creative Commons Attribution Share-Alike 4.0 License
SparkFun-Aesthetics: https://creativecommons.org/licenses/by-sa/4.0
